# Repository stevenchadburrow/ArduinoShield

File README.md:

# ArduinoShield

This project is designed to make an Arduino into a standalone microcomputer.

Runs the Arduino Uno at the standard 16 MHz.  The shield gives the ATMega238 microcontroller up to 16KB of additional RAM. VGA output of 512x240 monochrome character display, allowing for 64-column text.  Also supports PS/2 Keyboard input and square wave audio output.

This uses the Xilinx XC9572XL CPLD, programmed using Xilinx ISE and 'xc3sprog'.

BASIC and a Roguelike Game were created for the system.

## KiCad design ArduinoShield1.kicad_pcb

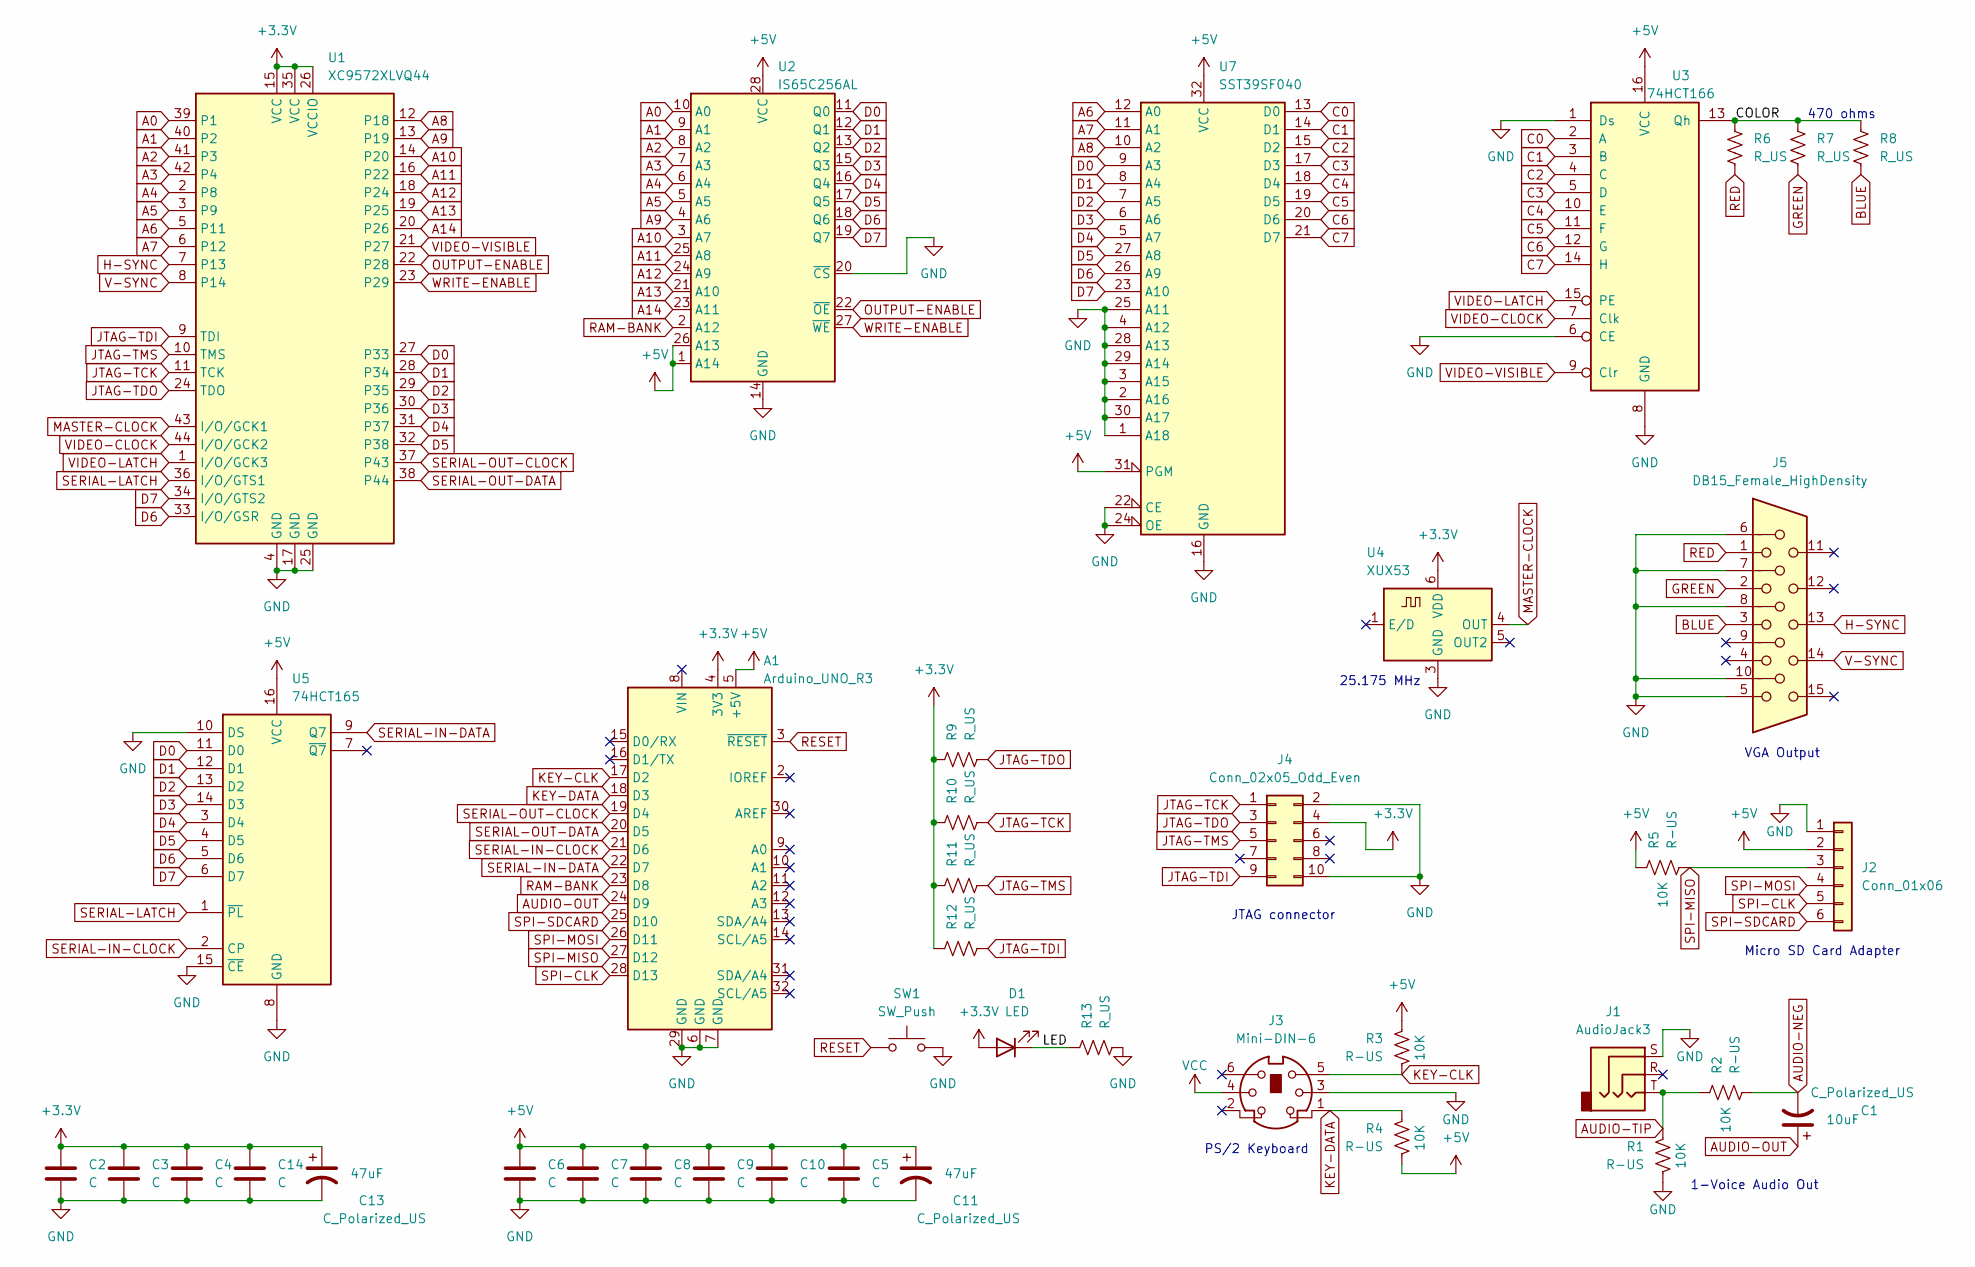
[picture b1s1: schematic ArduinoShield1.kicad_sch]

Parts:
A1: Arduino_UNO_R3
C1: C_Polarized_US; CP_Elec_4x5.4
C2, C3, C4, C5, C6, C7, C8, C9, C10, C14: C; C_0805_2012Metric_Pad1.18x1.45mm_HandSolder
C11, C13: C_Polarized_US; CP_Elec_5x5.4
D1: LED; LED_1206_3216Metric_Pad1.42x1.75mm_HandSolder
J1: AudioJack3; Jack_3.5mm_CUI_custom_SJ-3524-SMT_Horizontal
J2: Conn_01x06; PinSocket_custompin1_1x06_P2.54mm_Vertical
J3: Mini-DIN-6; PS2_Din6
J4: Conn_02x05_Odd_Even; PinHeader_2x05_P2.54mm_Vertical
J5: DB15_Female_HighDensity; DSUB-15-HD_Female_Horizontal_P2.29x2.54mm_VGA
R1, R2, R3, R4, R5: R-US; R_0805_2012Metric_Pad1.20x1.40mm_HandSolder
R6, R7, R8, R9, R10, R11, R12: R_US; R_0805_2012Metric_Pad1.20x1.40mm_HandSolder
R13: R_US; R_1206_3216Metric_Pad1.30x1.75mm_HandSolder
SW1: SW_Push; SW_Push_1P1T_NO_CK_KMR2
U1: XC9572XLVQ44; TQFP-44_10x10mm_P0.8mm
U2: IS65C256AL; SOIC-28W_custom_7.5x18.7mm_P1.27mm
U3: 74HCT166; SOIC-16_4.55x10.3mm_P1.27mm
U4: XUX53; Oscillator_SMD_IDT_JS6-6_5.0x3.2mm_P1.27mm
U5: 74HCT165; SOIC-16_4.55x10.3mm_P1.27mm
U7: SST39SF040; PLCC-32_THT-Socket

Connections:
+3.3V: A1.4 (3V3), C2.1, C3.1, C4.1, C13.1, C14.1, D1.2 (A), J4.4, R9.1, R10.1, R11.1, R12.1, U1.15 (VCC), U1.26 (VCCIO), U1.35 (VCC), U4.6 (VDD)
/COLOR: R6.1, R7.1, R8.1, U3.13 (Qh)
/LED: D1.1 (K), R13.1
A0: U1.39 (P1), U2.10 (A0)
A1: U1.40 (P2), U2.9 (A1)
A2: U1.41 (P3), U2.8 (A2)
A3: U1.42 (P4), U2.7 (A3)
A4: U1.2 (P8), U2.6 (A4)
A5: U1.3 (P9), U2.5 (A5)
A6: U1.5 (P11), U7.12 (A0)
A7: U1.6 (P12), U7.11 (A1)
A8: U1.12 (P18), U7.10 (A2)
A9: U1.13 (P19), U2.4 (A6)
A10: U1.14 (P20), U2.3 (A7)
A11: U1.16 (P22), U2.25 (A8)
A12: U1.18 (P24), U2.24 (A9)
A13: U1.19 (P25), U2.21 (A10)
A14: U1.20 (P26), U2.23 (A11)
AUDIO-NEG: C1.2, R2.2
AUDIO-OUT: A1.24 (D9), C1.1
AUDIO-TIP: J1.T, R1.1, R2.1
BLUE: J5.3, R8.2
C0: U3.2 (A), U7.13 (D0)
C1: U3.3 (B), U7.14 (D1)
C2: U3.4 (C), U7.15 (D2)
C3: U3.5 (D), U7.17 (D3)
C4: U3.10 (E), U7.18 (D4)
C5: U3.11 (F), U7.19 (D5)
C6: U3.12 (G), U7.20 (D6)
C7: U3.14 (H), U7.21 (D7)
D0: U1.27 (P33), U2.11 (Q0), U5.11 (D0), U7.9 (A3)
D1: U1.28 (P34), U2.12 (Q1), U5.12 (D1), U7.8 (A4)
D2: U1.29 (P35), U2.13 (Q2), U5.13 (D2), U7.7 (A5)
D3: U1.30 (P36), U2.15 (Q3), U5.14 (D3), U7.6 (A6)
D4: U1.31 (P37), U2.16 (Q4), U5.3 (D4), U7.5 (A7)
D5: U1.32 (P38), U2.17 (Q5), U5.4 (D5), U7.27 (A8)
D6: U1.33 (I/O/GSR), U2.18 (Q6), U5.5 (D6), U7.26 (A9)
D7: U1.34 (I/O/GTS2), U2.19 (Q7), U5.6 (D7), U7.23 (A10)
GND: A1.6 (GND), A1.7 (GND), A1.29 (GND), C2.2, C3.2, C4.2, C5.2, C6.2, C7.2, C8.2, C9.2, C10.2, C11.2, C13.2, C14.2, J1.S, J2.1, J3.3, J4.2, J4.10, J5.5, J5.6, J5.7, J5.8, J5.10, R1.2, R13.2, SW1.2, U1.4 (GND), U1.17 (GND), U1.25 (GND), U2.14 (GND), U2.20 (~CS), U3.1 (Ds), U3.6 (CE), U3.8 (GND), U4.3 (GND), U5.8 (GND), U5.10 (DS), U5.15 (~CE), U7.1 (A18), U7.2 (A16), U7.3 (A15), U7.4 (A12), U7.16 (GND), U7.22 (CE), U7.24 (OE), U7.25 (A11), U7.28 (A13), U7.29 (A14), U7.30 (A17)
GREEN: J5.2, R7.2
H-SYNC: J5.13, U1.7 (P13)
JTAG-TCK: J4.1, R10.2, U1.11 (TCK)
JTAG-TDI: J4.9, R12.2, U1.9 (TDI)
JTAG-TDO: J4.3, R9.2, U1.24 (TDO)
JTAG-TMS: J4.5, R11.2, U1.10 (TMS)
KEY-CLK: A1.17 (D2), J3.5, R3.2
KEY-DATA: A1.18 (D3), J3.1, R4.1
MASTER-CLOCK: U1.43 (I/O/GCK1), U4.4 (OUT)
OUTPUT-ENABLE: U1.22 (P28), U2.22 (~OE)
RAM-BANK: A1.23 (D8), U2.2 (A12)
RED: J5.1, R6.2
RESET: A1.3 (~RESET), SW1.1
SERIAL-IN-CLOCK: A1.21 (D6), U5.2 (CP)
SERIAL-IN-DATA: A1.22 (D7), U5.9 (Q7)
SERIAL-LATCH: U1.36 (I/O/GTS1), U5.1 (~PL)
SERIAL-OUT-CLOCK: A1.19 (D4), U1.37 (P43)
SERIAL-OUT-DATA: A1.20 (D5), U1.38 (P44)
SPI-CLK: A1.28 (D13), J2.5
SPI-MISO: A1.27 (D12), J2.3, R5.2
SPI-MOSI: A1.26 (D11), J2.4
SPI-SDCARD: A1.25 (D10), J2.6
V-SYNC: J5.14, U1.8 (P14)
VIDEO-CLOCK: U1.44 (I/O/GCK2), U3.7 (Clk)
VIDEO-LATCH: U1.1 (I/O/GCK3), U3.15 (PE)
VIDEO-VISIBLE: U1.21 (P27), U3.9 (Clr)
WRITE-ENABLE: U1.23 (P29), U2.27 (~WE)

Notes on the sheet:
PS/2 Keyboard
JTAG connector
1-Voice Audio Out
Micro SD Card Adapter
VGA Output
25.175 MHz
470 ohms

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
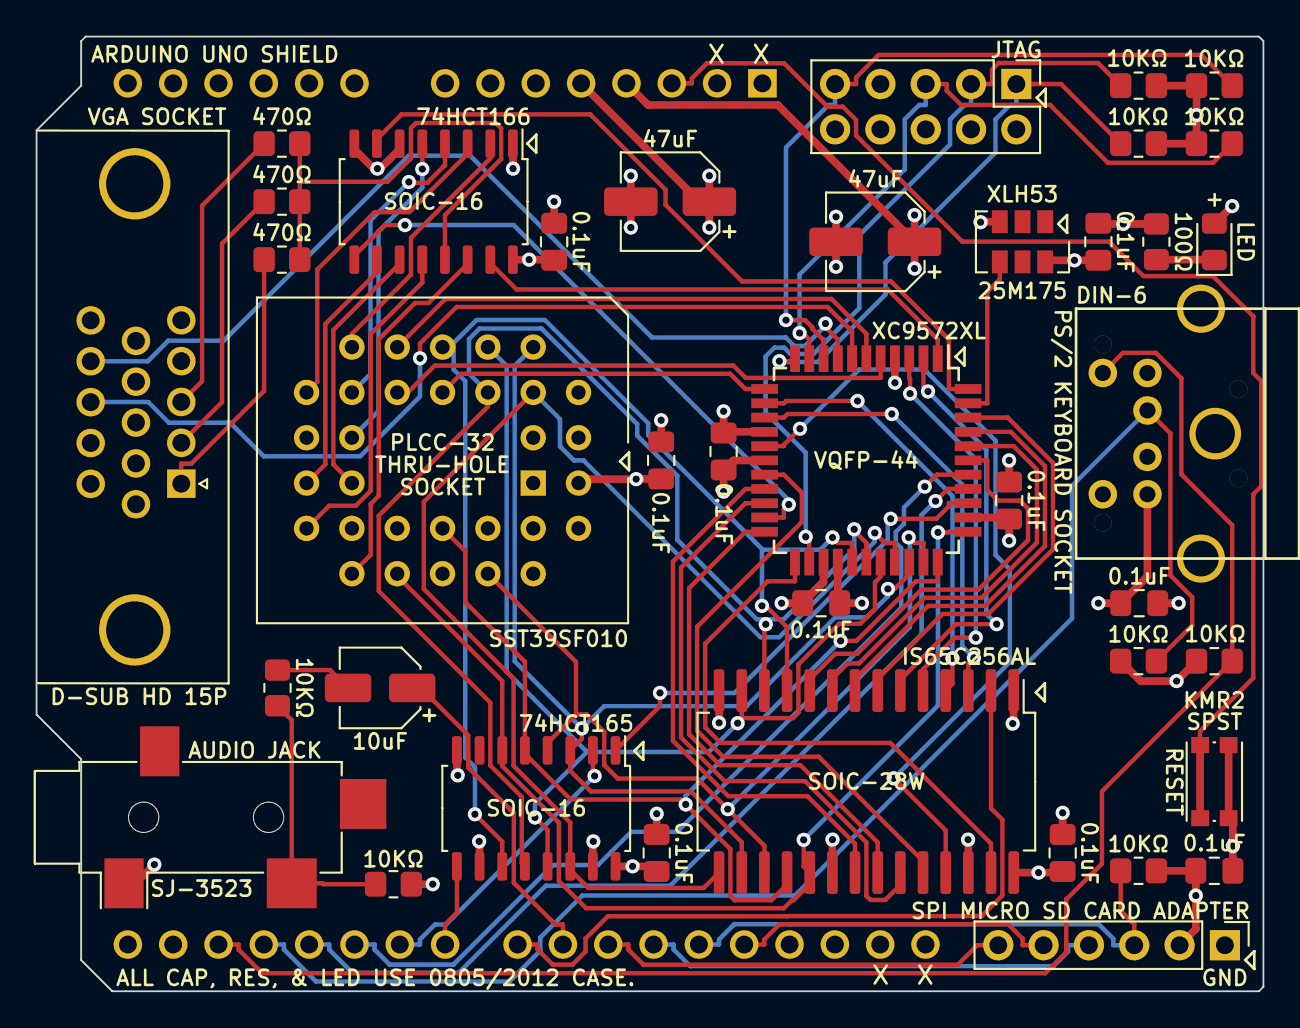
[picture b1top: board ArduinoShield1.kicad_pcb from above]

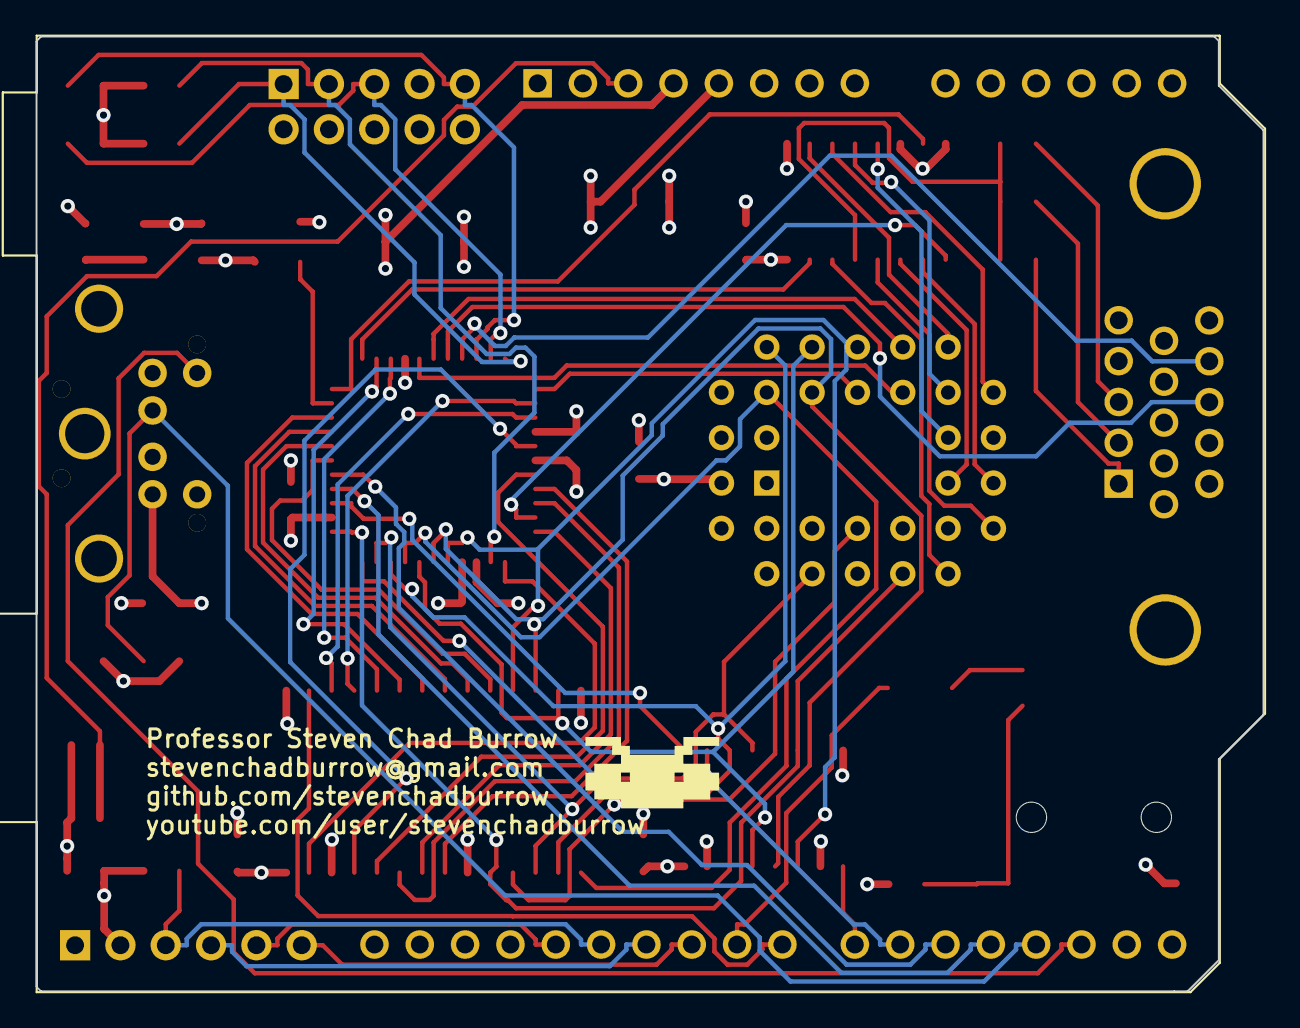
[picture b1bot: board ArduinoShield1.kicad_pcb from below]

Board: 4 copper layers, 68.8 x 53.5 mm, 41 parts (2 on the bottom side), 67 nets.

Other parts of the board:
G100: LOGO; Mystery
